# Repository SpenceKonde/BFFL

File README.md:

BFFL
====

Code and hardware specs for Big F'n FlashLight (BFFL)

Concept
====

The BFFL represents the extension of commercially available high power LED flashlights to their illogical conclusion. The BFFL uses a 150W LED emitter, and is powered by 24 18650 lithium ion batteries. The BFFL easily outshines typical home outdoor spotlights. 

Control
====
Control is provided by an ATtiny84 microcontroller. Control inputs consist of a trigger, brightness control, and standby light.  Brightness is adjustable down to 1/32 power via PWM, and it can set to run at 1/32 to 1/8 power when the trigger is not depressed (so you can find your way with it pointed down, and then press the trigger to get a much brighter search light) Battery status is displayed via an RGB led, and the temperature of the emitter is monitored to prevent overheating in the event of a cooling failure. The fan used has PWM control, and the speed of the fan is controlled by the measured temperature.

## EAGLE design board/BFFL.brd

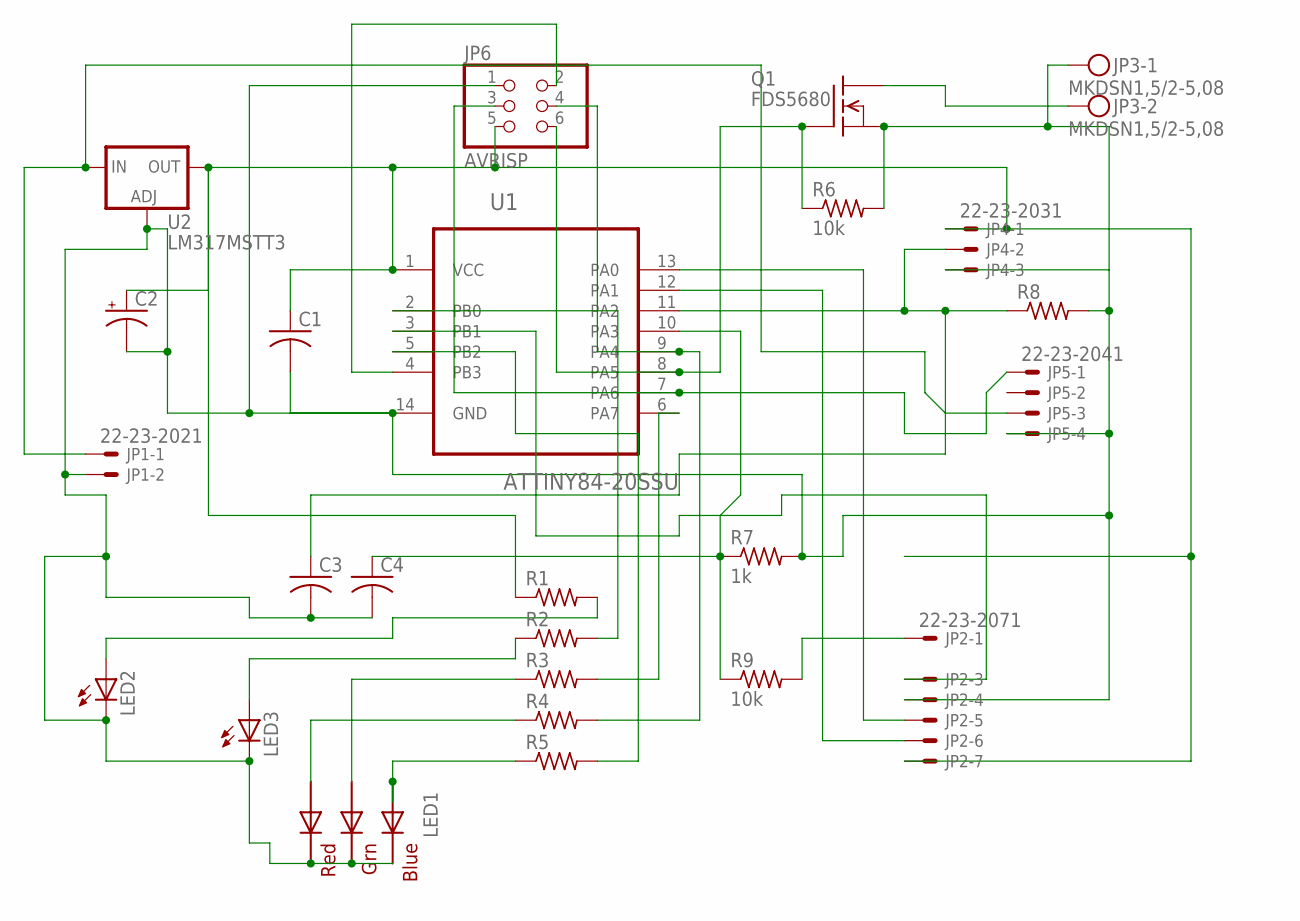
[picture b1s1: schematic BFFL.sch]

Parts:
C1, C3, C4: C-USC1206K; C1206K
C2: CPOL-USC/6032-28W; C/6032-28W
JP1: 22-23-2021
JP2: 22-23-2071
JP3: MKDSN1,5/2-5,08
JP4: 22-23-2031
JP5: 22-23-2041
JP6: AVRISP; 2X03
LED1: RGBLED5050
LED2, LED3: LEDCHIPLED_1206; CHIPLED_1206
Q1: FDS5680; SO-8
R1, R2, R3, R4, R5, R8: R-US_R1206; R1206
R6, R9: 10k; R1206
R7: 1k; R1206
U1: ATTINY84-20SSU; SOIC127P600X175-14N
U2: LM317MSTT3; SOT223

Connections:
unnamed: JP2.1, R9.2
unnamed: C4.1, R7.1, R9.1, U1.10 (PA3)
unnamed: JP1.1, JP5.3, U2.3 (IN)
unnamed: JP6.6, Q1.4 (G), R6.1, U1.8 (PA5)
unnamed: R2.2, U1.2 (PB0)
unnamed: C1.1, C2.+, JP2.7, JP4.1, JP6.5, R1.1, U1.1 (VCC), U2.4 (OUT)
unnamed: LED2.A, R1.2
unnamed: LED3.A, R2.1
unnamed: LED1.2 (RED_A), R4.1
unnamed: LED1.1 (GREEN_A), R3.1
unnamed: LED1.3 (BLUE_A), R5.1
unnamed: JP3.2, Q1.5 (D), Q1.6 (D), Q1.7 (D), Q1.8 (D)
unnamed: C1.2, C2.-, C3.2, C4.2, JP1.2, JP2.4, JP3.1, JP4.3, JP5.4, JP6.1, LED1.4 (BLUE_C), LED1.5 (RED_C), LED1.6 (GREEN_C), LED2.C, LED3.C, Q1.1 (S), Q1.2 (S), Q1.3 (S), R6.2, R7.2, R8.2, U1.14 (GND), U2.1 (ADJ)
unnamed: R5.2, U1.5 (PB2)
unnamed: R3.2, U1.6 (PA7)
unnamed: JP5.1, JP6.3, U1.7 (PA6)
unnamed: JP2.3, U1.3 (PB1)
unnamed: JP6.4, R4.2, U1.9 (PA4)
unnamed: C3.1, JP4.2, R8.1, U1.11 (PA2)
unnamed: JP2.5, U1.13 (PA0)
unnamed: JP2.6, U1.12 (PA1)
unnamed: JP6.2, U1.4 (PB3)

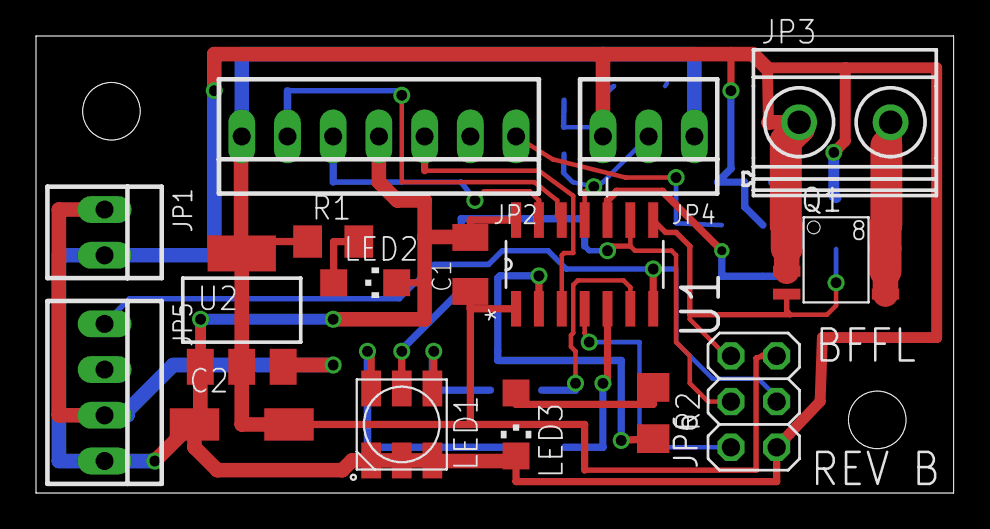
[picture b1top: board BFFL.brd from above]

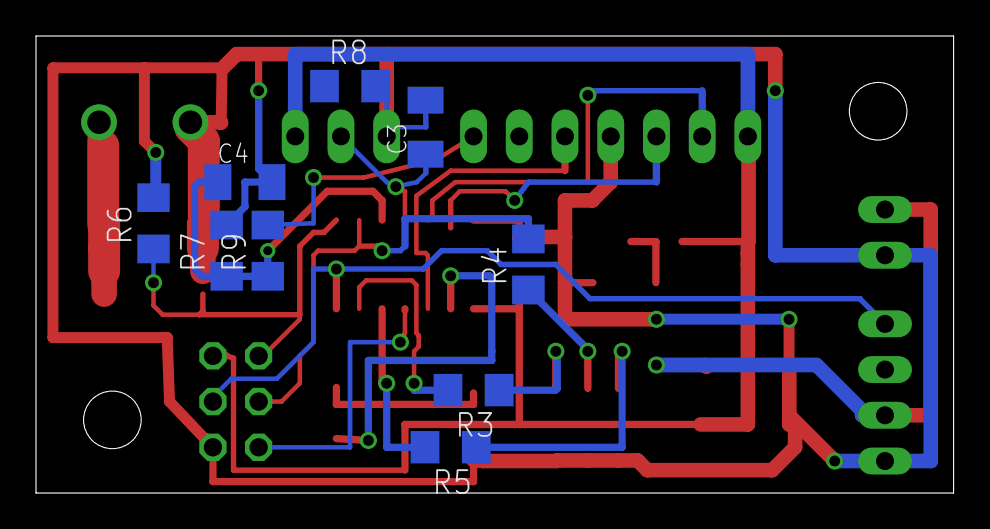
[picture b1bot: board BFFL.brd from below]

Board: 2 copper layers, 51.0 x 25.4 mm, 25 parts (9 on the bottom side), 22 nets.

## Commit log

2014-07-01 Initial commit
    6/30 version of code and eeprom for the Big Fuckin' FlashLight
2014-07-01 Organize, add eagle files
2014-07-11 Update Part List.md
    Formatted, added errata.
2014-07-13 Rev B of PCB, preliminary
    Corrects multiple faults in Rev A and improves mounting options.
    Silkscreen still needs to be done.
2014-07-15 Update board
2014-07-15 Move sketch into folder
    This allows the arduino IDE to open it without having to move the file
    around manually.
